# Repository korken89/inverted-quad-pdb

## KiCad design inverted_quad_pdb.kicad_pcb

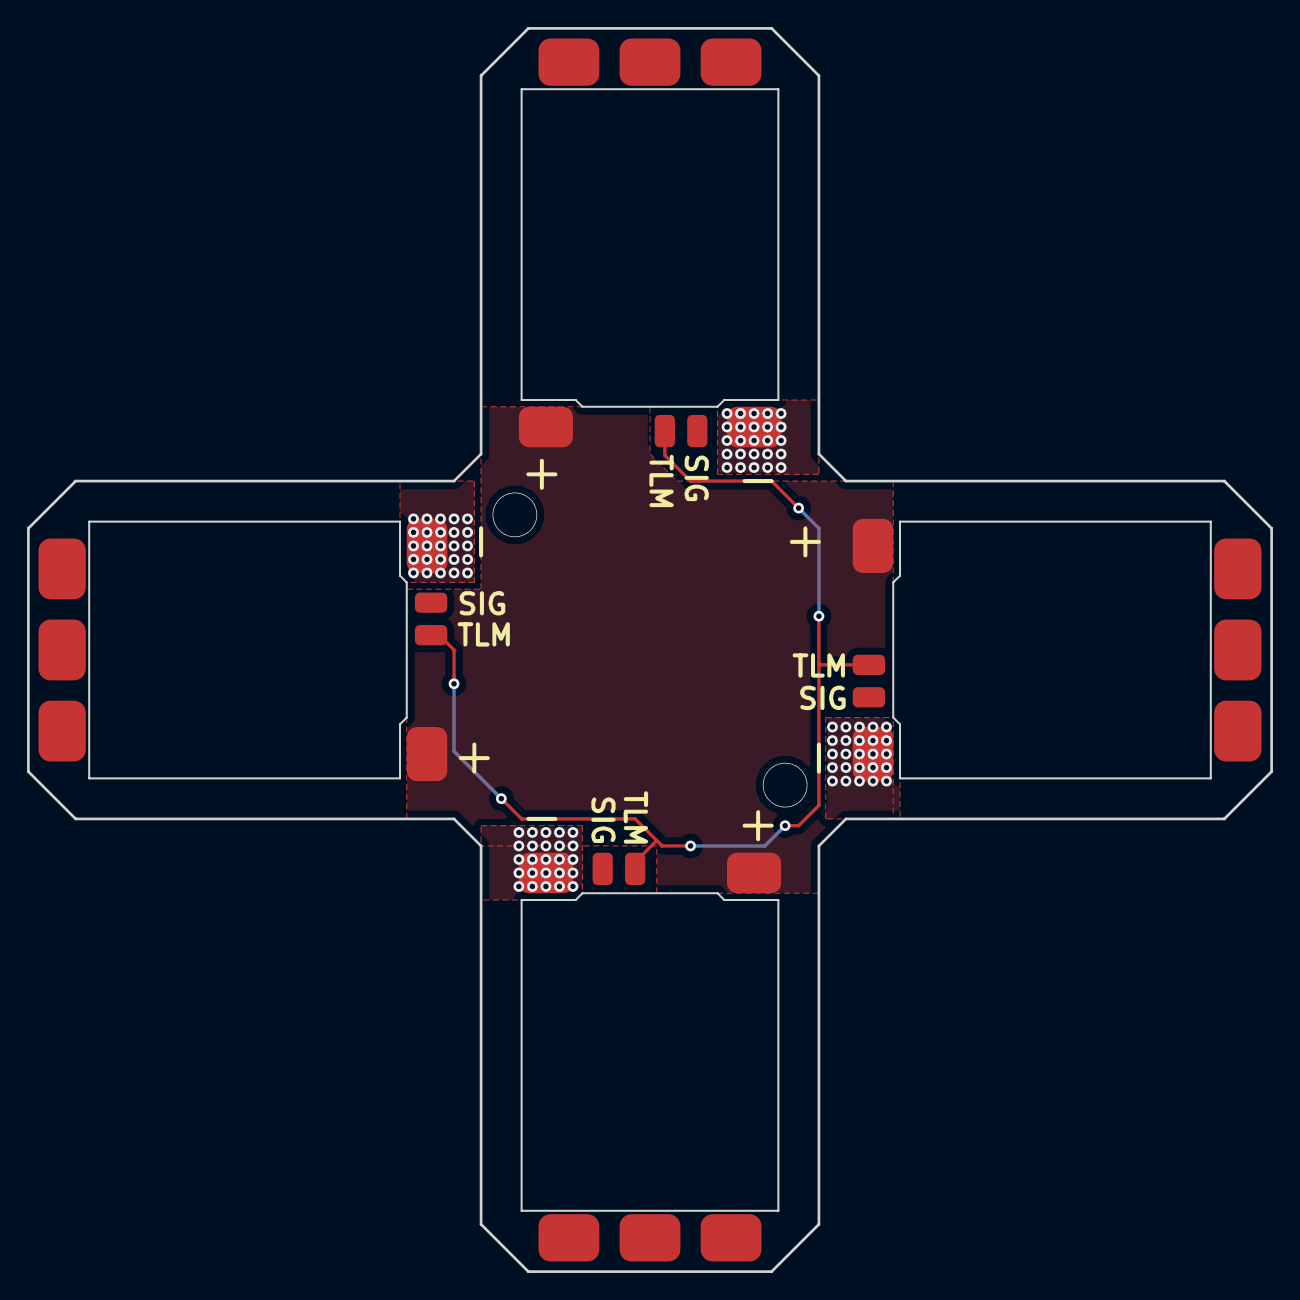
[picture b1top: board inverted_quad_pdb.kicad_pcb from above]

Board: 2 copper layers, 92.0 x 92.0 mm, 4 parts (0 on the bottom side), 3 nets.

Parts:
ESC1, ESC2, ESC3, ESC4: KISS_ESC_24A; kiss_esc_24a

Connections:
+BATT: ESC1.1, ESC2.1, ESC3.1, ESC4.1
/TLM: ESC1.2, ESC2.2, ESC3.2, ESC4.2
GND: ESC1.4, ESC2.4, ESC3.4, ESC4.4

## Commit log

2018-09-11 v1.0 send for order
